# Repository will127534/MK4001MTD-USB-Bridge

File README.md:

# MK4001MTD USB Bridge

**RP2040 Pico firmware that bridges a Toshiba MK4001MTD 0.85" SDIO microdrive as a USB Mass Storage device.**

The MK4001MTD is a 4 GB Microdrive originally used in the Nokia N91 music phone and some other devices, like MP3 players or USB drives, back when flash storage was still quite expensive.

You might have seen introductions claiming this drive uses the MMC protocol, but that’s actually incorrect. I’ve been investigating this for a while: I tried building an 8-bit MMCplus card reader and tested different SD/MMC readers without success. As a last resort, I bought a Nokia N91 to capture logic traces and confirm what protocol it actually uses.

Here is the photo when I was trying to use it with my 8bit-MMCPlus reader board, and it turns out it is not MMC :(

So I end up getting N91 to collect traces:

Unlike standard ATA/CF Microdrives, it uses an SDIO interface with ATA commands tunneled through CMD52/CMD53. No existing driver supports this protocol, so this firmware implements the full stack from scratch.

This surprised me, because there is an SDIO-to-ATA standard called CE-ATA. But if you look closely at the release timeline, CE-ATA came later than this drive. As a result, this drive relies entirely on SDIO commands, and CE-ATA is not available. CE-ATA has two new cmd CMD60/CMD61 and utilize CMD12/39, but you can see from the traces it is not using any of those.  

The second hardware point to mention is that another piece of misinformation floating around—claiming it’s an 8-bit MMCPlus card—is not only untrue, but the pinout doesn’t follow the MMC standard either. You can find the Nokia N91 service manual with some documentation on the pinout: while the pin numbering follows the MMCPlus standard, the pin mapping does not. This is an important detail if you’re wiring it yourself: it uses the same MMC connector, but the pin mapping is different, more in the Hardware section.

Finally, note that this is co-developed with Claude/OpenClaw. I collected the logic traces manually and set up a closed-loop test station for OpenClaw to iterate on development—analyzing the traces and implementing features. The documentation will mostly be written by Claude; I’ll add my notes inline as well. I’ve also read and double-checked the documentation myself, and it should be reliable and easy to follow.

For insights into the analytics on N91 trace, it is under /docs/N91_TRACE_ANALYSIS.md, I've also put the N91 service manual there along with the raw logic traces.

See more in the blog post here: [https://www.willwhang.dev/Reading-MK4001MTD/](https://www.willwhang.dev/Reading-MK4001MTD/)  
See it in activity here: [https://youtu.be/GC4xil3_Bbc](https://youtu.be/GC4xil3_Bbc)

## Status

Fully functional USB mass storage with PIO-accelerated reads/writes and idle power management.

| Metric | Value |
|--------|-------|
| Read speed | ~985 kB/s (USB full-speed limited) |
| Write speed | ~920 kB/s (USB full-speed limited, advertised write cache) |
| Raw SDIO-side speed | ~2.35 MB/s read / ~2.15 MB/s write (drive-limited) |
| Capacity | 3.75 GB (7,862,400 sectors) |
| Filesystem | FAT32 verified (mount/unmount/fsck clean) |
| Data integrity | Write+readback verified; per-block CRC16 on all 4 DAT lines |
| Idle standby | 5 s idle or USB suspend → STANDBY IMMEDIATE + power gate |

## How It Works

### Architecture

```
USB Host ←→ USB MSC (TinyUSB) ←→ ATA Layer ←→ SDIO Layer (PIO) ←→ MK4001MTD
```

The firmware has four layers:

1. **USB MSC** (`msc_device.c`) — TinyUSB Mass Storage Class. Translates SCSI READ(10)/WRITE(10) into ATA sector operations. 32 KB EP buffer, batching up to 64 sectors per USB transfer. Drive I/O is overlapped with USB in both directions, like a real ATA-USB bridge with a caching disk: a sequential-read prefetcher fetches the next chunk while the previous one streams to the host, and writes are staged and flushed while USB receives the next piece. The device advertises its write cache (Caching mode page, WCE=1 — hosts report "Write cache: enabled" and issue SYNCHRONIZE CACHE at fsync/unmount/suspend, which the firmware honors). A failed background flush surfaces as MEDIUM ERROR on the next WRITE or SYNCHRONIZE CACHE; writes to known-bad sectors take a strict synchronous path.

2. **ATA-over-SDIO** (`ata_sdio.c`) — Implements ATA commands (IDENTIFY, READ SECTORS, WRITE SECTORS) by writing to ATA registers mapped into SDIO function 1 address space via CMD52, and transferring sector data via CMD53. 3-tier retry logic at CMD, data, and ATA levels.

3. **PIO SDIO** (`sdio_pio.c`, `sdio.pio`) — Hardware-accelerated SDIO using RP2040's PIO peripheral (4-bit bus at 10 MHz, 4 PIO cycles per bit with input synchronizers bypassed). Three PIO programs share a single state machine via dynamic program swapping:
   - **CMD tx/rx** (24 instructions) — sends SDIO commands and receives responses
   - **DAT read** (12 instructions) — reads data blocks from 4-bit DAT bus via byte-swapping DMA (no CPU repack); block N's CRC verifies while block N+1 streams
   - **DAT write** (14 instructions) — writes data blocks to 4-bit DAT bus via DMA, with built-in CRC status reception and busy-wait; block N+1's nibble stream builds while block N transfers

4. **Pin/Power** (`sdio_hw.c`) — GPIO initialization and HDD power control. All SDIO communication uses PIO.

Human notes: Interestingly, Claude was really reluctant to implement SDIO in PIO, and a lot of development cycles were wasted bouncing back and forth between PIO and bit-banging.

### The SDIO-ATA Protocol

The MK4001MTD presents itself as an SDIO card with one I/O function. Standard SDIO card initialization (CMD5/CMD3/CMD7) sets up the bus, then ATA registers are accessed through SDIO commands:

**Register access (CMD52):** Each ATA register is mapped to a function 1 address:

| Address | Register | Usage |
|---------|----------|-------|
| 0x00 | DATA | CMD53 target for sector data |
| 0x01 | ERR/FEAT | Error (read) / Feature (write) |
| 0x02 | SECCOUNT | Sector count |
| 0x03 | LBA_LO | LBA bits 0-7 |
| 0x04 | LBA_MID | LBA bits 8-15 |
| 0x05 | LBA_HI | LBA bits 16-23 |
| 0x06 | DEV/HEAD | Device/Head + LBA bits 24-27 |
| 0x07 | CMD/STATUS | Command (write) / Status (read) |

**Data transfer (CMD53):** Sector data is transferred by issuing CMD53 in block mode targeting the DATA register (address 0x00). For multi-sector reads, a single CMD53 with `block_count=N` transfers N × 512 bytes in one SDIO multi-block transaction.

**Interrupt signaling:** The drive signals sector readiness by asserting an SDIO interrupt (INT_PENDING bit 1 in CCCR register 0x05). Reading the ATA STATUS register clears the interrupt.

### Read Path (Multi-Block PIO)

For a 16-sector read:

```
1. Write ATA registers via PIO CMD52:
     SECCOUNT=16, LBA_LO/MID/HI, DEV/HEAD=0xE0, CMD=0x20

2. Poll STATUS via CMD52 until DRQ (bit 3) is set

3. Swap PIO to DAT read program
4. Send CMD53: block_mode=1, fn=1, addr=0x0000, block_count=16

5. PIO DAT read: for each of the 16 blocks:
   a. Wait for start bit (all DAT lines low)
   b. DMA 1024 nibbles (512 bytes) from PIO RX FIFO to buffer
   c. Wait for SM to finish clocking CRC+end nibbles (poll SM PC)
   d. Repack nibbles → bytes in-place

6. Swap PIO back to CMD program
```

### Write Path (Multi-Block PIO)

For a 16-sector write:

```
1. Write ATA registers via PIO CMD52:
     SECCOUNT=16, LBA, DEV/HEAD=0xE0, CMD=0x30

2. Poll STATUS via CMD52 until DRQ (bit 3) is set
   (STATUS 0xD8 = BSY+DRQ treated as DRQ-ready, per N91 trace)

3. Swap PIO to DAT write program
4. Send CMD53: block_mode=1, fn=1, addr=0x0000, block_count=16

5. PIO DAT write: for each of the 16 blocks:
   a. Precompute CRC16-CCITT per DAT line (4 independent CRCs)
   b. Build nibble stream: start(0x0) + data(1024 nibbles) + CRC(16) + end(0xF)
   c. DMA nibble stream to PIO TX FIFO
   d. PIO clocks out all nibbles, then:
      - Switches DAT to input
      - Clocks 16 cycles for CRC status from card
      - Polls DAT0 until card releases busy
      - Fires IRQ 0 to signal block completion

6. Swap PIO back to CMD program
```

### PIO Program Swapping

The RP2040 PIO has 32 instruction slots per block. Our three programs total 55 instructions, so they can't coexist. Instead, a single SM0 on PIO0 is used, and programs are swapped by writing directly to PIO instruction memory:

```c
static void load_program_raw(const pio_program_t *program) {
    for (uint i = 0; i < program->length; i++)
        pio->instr_mem[FIXED_OFFSET + i] = program->instructions[i];
}
```

This bypasses the SDK's `pio_add_program`/`pio_remove_program` allocator. Program swap takes ~1 µs. Each swap is followed by a program-specific reinit that sets pin mappings, shift direction, and clock divider.

### Power Management

Analysis of Nokia N91 logic traces reveals aggressive power management:

- **Idle mode:** STANDBY IMMEDIATE (0xE0) every **~7.5 seconds**, even with no I/O. Each standby triggers full SDIO re-initialization (CMD5 retry → CMD3 → CMD7 → CCCR setup). 28 standby cycles observed in one idle session.
- **Active mode:** Standby issued between bursts of I/O (24 cycles during USB drive file operations).
- No other power commands (IDLE, SLEEP, CHECK POWER MODE) or CCCR power register accesses observed.

The firmware replicates this behavior with a configurable idle timeout:

```c
#define IDLE_STANDBY_MS 5000  // in main.c
```

Two paths trigger HDD power gating:

1. **Idle timeout** (5 seconds) — main loop detects no I/O activity
2. **USB suspend** — host suspends the USB port

Both paths send ATA STANDBY IMMEDIATE (0xE0) to flush the write cache and park heads, then cut power via GP9.

**Wake sequence** (triggered by first READ/WRITE after gate):
1. Power on HDD, wait 500ms for rail settling
2. PIO-based SDIO reinit: CMD5 (OCR) → 10ms settle → CMD3 (RCA) → CMD7 (select)
3. Switch to fast PIO clock, configure CCCR via CMD52 (4-bit bus, 512B blocks, fn1 enable)
4. Poll fn1 ready (CCCR IO_READY bit 1)
5. N91-style 30ms DRDY status poll until drive is ATA-ready

### Bad Sector Handling

When a multi-sector transfer hits a bad sector:
1. Chunk read fails → error recovery (IO_ABORT + fn1 reset, ~500ms)
2. Falls back to per-sector I/O to identify the failing block precisely
3. The ATA layer waits long enough to capture the final `STATUS/ERROR` bits instead of collapsing the failure into a generic `DRQ timeout`
4. Any unrecovered block fails the SCSI command immediately with `MEDIUM ERROR` (read: 03/11/00, write: 03/0C/00)
5. Bad-sector LBA cached → repeat *reads* fail quickly without re-hammering the drive (anti-hammer protection against host retry storms)
6. *Writes* always touch the medium, per SBC — a successful write to a cached-bad LBA clears it from the cache, exactly like a drive clearing a pending sector

Point 6 is not academic: this drive had a long-standing unreadable sector at `LBA 1952` (`READ: ST=0x51 ERR ERR=0x40 UNC`). Once the bridge allowed a write to actually reach it, the drive rewrote the sector and it has read back cleanly since:

```text
[ATA] FAST-RD: ST=0x51 ERR ERR=0x40 UNC LBA=1952
[MSC] BAD SECTOR read LBA=1952
[MSC] Bad sector LBA=1952 repaired by write
```

## Building

### Prerequisites

- Raspberry Pi Pico SDK — **stock, unmodified, pinned to 2.2.0**
- ARM toolchain (`arm-none-eabi-gcc`)
- CMake

The SDK version is **locked**: if `PICO_SDK_PATH` is set (environment or
CMake variable) it is used and its version is checked against the pin —
a mismatch fails the configure with instructions (override with
`-DMK4001_ALLOW_SDK_MISMATCH=ON`). With no `PICO_SDK_PATH` at all, the
pinned SDK release is fetched from GitHub automatically at configure
time, so a bare `git clone && cmake && make` is fully reproducible.

The firmware needs a patched TinyUSB MSC class driver (app sense data
preserved on read/write errors + a Caching mode page with WCE=1). That
file is **vendored in this repo** at `lib/tinyusb_patched/msc_device.c` —
the build automatically compiles it instead of the SDK's copy, so no SDK
surgery is ever needed. The diff against upstream TinyUSB (0.18.0, as
bundled with pico-sdk 2.2.0) is in `lib/tinyusb_patched/`; the SDK pin
exists precisely because this vendored file must track the SDK's TinyUSB.

### Build & Flash

```bash
cd /home/pi/mk4001_bridge/build
cmake ..
make -j4

sudo openocd -f interface/cmsis-dap.cfg -f target/rp2040.cfg \
  -c "adapter speed 1000" -c "init" -c "reset halt" -c "sleep 200" \
  -c "program /home/pi/mk4001_bridge/build/mk4001_bridge.elf verify" \
  -c "reset run" -c "exit"
```

### Hardware Wiring

| Pico GPIO | Function | Notes |
|-----------|----------|-------|
| GP2 | SDIO_CLK | Host clock output |
| GP3 | SDIO_CMD | Bidirectional command line |
| GP4 | SDIO_DAT0 | Data bit 0 |
| GP5 | SDIO_DAT1 | Data bit 1 |
| GP6 | SDIO_DAT2 | Data bit 2 |
| GP7 | SDIO_DAT3 | Data bit 3 |
| GP9 | HDD_EN | Drive power enable (HIGH=on) |
| GP12 | UART TX | Debug output @ 115200 |
| GP13 | UART RX | Debug input |
| GP16 | LED: HDD Power | Active low |
| GP17 | LED: HDD Healthy | Active low |
| GP18 | LED: Read | Active low |
| GP19 | LED: Write | Active low |

**Note:** GP0 and GP1 are dead on this specific Pico unit. All SDIO pin assignments are shifted +2.

Human notes: Claude was wrong here because it didn’t realize that GP0 and GP1 were being used for the UART terminal in its build configuration. It kept forgetting this, to the point where I just moved the SDIO GPIOs off that UART.

HDD_PWR isn’t necessary. You don’t have to power-cycle the drive to use it; it’s more of a development convenience for resetting the HDD when a lot of things are hard-coded. That said, if you want power savings, you can use that signal, but it can handle warm reset without any issue.

You’ll see debug messages over UART. They’re not going through USB-CDC because it was easier for Claude to set up a separate UART-to-USB logging link that doesn’t disconnect or become unstable during early development.

The UART log also reports the **drive temperature** every 30 seconds while the drive is active (`[TEMP] drive temperature: 29 C`). The sensor was discovered by reverse-engineering the Toshiba vendor command `0xC2` — the N91 reads it at the start of every drive session to enforce its HDD operating-temperature limits. Details in [`docs/N91_TRACE_ANALYSIS.md`](docs/N91_TRACE_ANALYSIS.md) §4.

Here is a example of the log:

```
========================================
  MK4001MTD USB Bridge v0.11
  SDIO-ATA → USB Mass Storage (PIO)
========================================

[MAIN] Pre-delay 5000ms...
[PIO] Init OK: clkdiv=3.12 (~10.0 MHz), CMD@0
[MAIN] Power cycling HDD...
[SDIO] HDD power OFF
[SDIO] HDD power ON
[MAIN] SDIO init (PIO)...
[SDIO] CMD5 ready (OCR=0x901F8000)
[SDIO] RCA=0x0001
[SDIO] fn1 ready (attempt 0)
[MAIN] ATA IDENTIFY...
[ATA] IDENTIFY complete
Model:    [TOSHIBA MK4001MTD]
Serial:   [           763B004HA]
Firmware: [VH173A]
Sectors:  7862400 (3839 MB)
SMART:    not supported (supported=0, enabled=0)
IDENTIFY: W0=0040 W47=0000 W49=0000 W59=0000
  ATA W80=0000  Cmd W82=0000 W83=0000 W84=0000
  En  W85=0000 W86=0000 W87=0000  W89=0008 W128=0001

[DIAG] === Drive Diagnostics ===
[DIAG] Standard SMART: not supported (IDENTIFY W82 bit0 = 0)
[DIAG] Toshiba vendor CMD 0xC2:
  FEAT=0x01 unknown_01                       → SC=00 LBA=02/00/00 ST=50
  FEAT=0x02 unknown_02                       â SC=00 LBA=02/00/00 ST=50
  FEAT=0x03 unknown_03                       → SC=00 LBA=02/00/00 ST=50
  FEAT=0x04 unknown_04                       → SC=00 LBA=02/00/00 ST=50
  FEAT=0x10 diag_10 (LBA_LO varies)          → SC=00 LBA=00/00/00 ST=50
  FEAT=0x11 diag_11                          → SC=00 LBA=00/00/00 ST=50
  FEAT=0x12 diag_12 (LBA_LO varies)          → SC=00 LBA=01/00/00 ST=50
  FEAT=0x20 query_20 (N91: SC=0xFF always)   → SC=FE LBA=00/FF/00 ST=50
  FEAT=0x21 query_21 (N91: SC varies per boot) → SC=1B LBA=00/FF/00 ST=50

[MAIN] MBR: valid 0x55AA
[MAIN] Warming up...
[MAIN] PIO OK, STATUS=0x50
[MAIN] Drive: 7862400 sectors (3839 MB)
[MAIN] Ready.
[PWR] Idle 5000ms → STANDBY + power gate
[PWR] STANDBY IMMEDIATE → power gate
[SDIO] HDD power OFF
```

Finally, here’s the wiring to the actual drive.  

Here is a crop from the N91 schematic, you can map the pin number also.

Side note that this is a 3V drive but I think 3.3V is fine, mostly it is to save some level shifting work.  

HW specifically designed for this drive is under /hardware!

## Source Files

| File | Lines | Purpose |
|------|-------|---------|
| `main.c` | 210 | Init, idle standby, USB suspend/resume |
| `msc_device.c` | 400 | USB MSC callbacks, power gate wake, bad sector cache |
| `ata_sdio.c` | 390 | ATA commands, error recovery, vendor diagnostics |
| `sdio_pio.c` | 635 | PIO SDIO: CMD52, CMD53 read/write, program swap, CRC16 |
| `sdio_hw.c` | 45 | Pin init + HDD power control |
| `sdio.pio` | 200 | PIO assembly + C SDK init helpers |
| `led.h` | 37 | LED helpers (GP16–GP19, active low) |
| `usb_descriptors.c` | 77 | USB device/config/string descriptors |
| `tusb_config.h` | 20 | TinyUSB config (MSC, 32KB EP buffer) |

## Version History

| Version | Read | Write | Key Change |
|---------|------|-------|------------|
| v0.1–v0.3 | 105 kB/s | 93 kB/s | Bit-bang SDIO, CRC16, retry logic |
| v0.5 | 374 kB/s | — | Single-SM PIO, direct instruction memory swap |
| v0.6 | 583 kB/s | 93 kB/s | Multi-block CMD53 reads, CRC clock drain fix |
| v0.8 | 588 kB/s | 274 kB/s | PIO writes, OSR flush fix |
| v0.9 | 475 kB/s | 371 kB/s | 64-sector chunks, CRC16 read verification |
| v0.10 | 453 kB/s | 329 kB/s | LED remap, HDD EN pin, UART on GP12/GP13 |
| v0.11 | ~450 kB/s | ~340 kB/s | HDD power gate, PIO wake, bad sector sense, USB suspend |
| **v0.12** | **~985 kB/s** | **~920 kB/s** | **Drive/USB overlap (read prefetch + advertised write cache with write-behind), pipelined PIO blocks, bswap DMA, 4-cycle PIO loops, SBC-style bad-sector semantics (write-repair), vendored TinyUSB MSC driver** |

## Testing

```bash
# Check device appeared
lsblk -dno NAME,MODEL | grep MK4001

# Filesystem test — mount, copy files, verify
sudo mount /dev/sdX1 /mnt/mk4001
cp /tmp/testfile /mnt/mk4001/
sync
md5sum /tmp/testfile /mnt/mk4001/testfile    # should match
sudo umount /mnt/mk4001

# Speed benchmarks (raw device, do NOT mount first — will corrupt filesystem)
# Use a safe offset past the filesystem or an unpartitioned drive
sudo dd if=/dev/sdX of=/dev/null bs=64k count=128 iflag=direct     # read
sudo dd if=/dev/zero of=/dev/sdX bs=64k count=64 oflag=direct seek=1024  # write (offset past FS)
```

Human notes here, fun fact: When it first starts to do speed testing, it actually dd directly to the drive and damage the filesystems..... Thankfully it doesn't matter that much here during the developments but always keep in mind when you handle OpenClaw your setup.

## License

I don't care.

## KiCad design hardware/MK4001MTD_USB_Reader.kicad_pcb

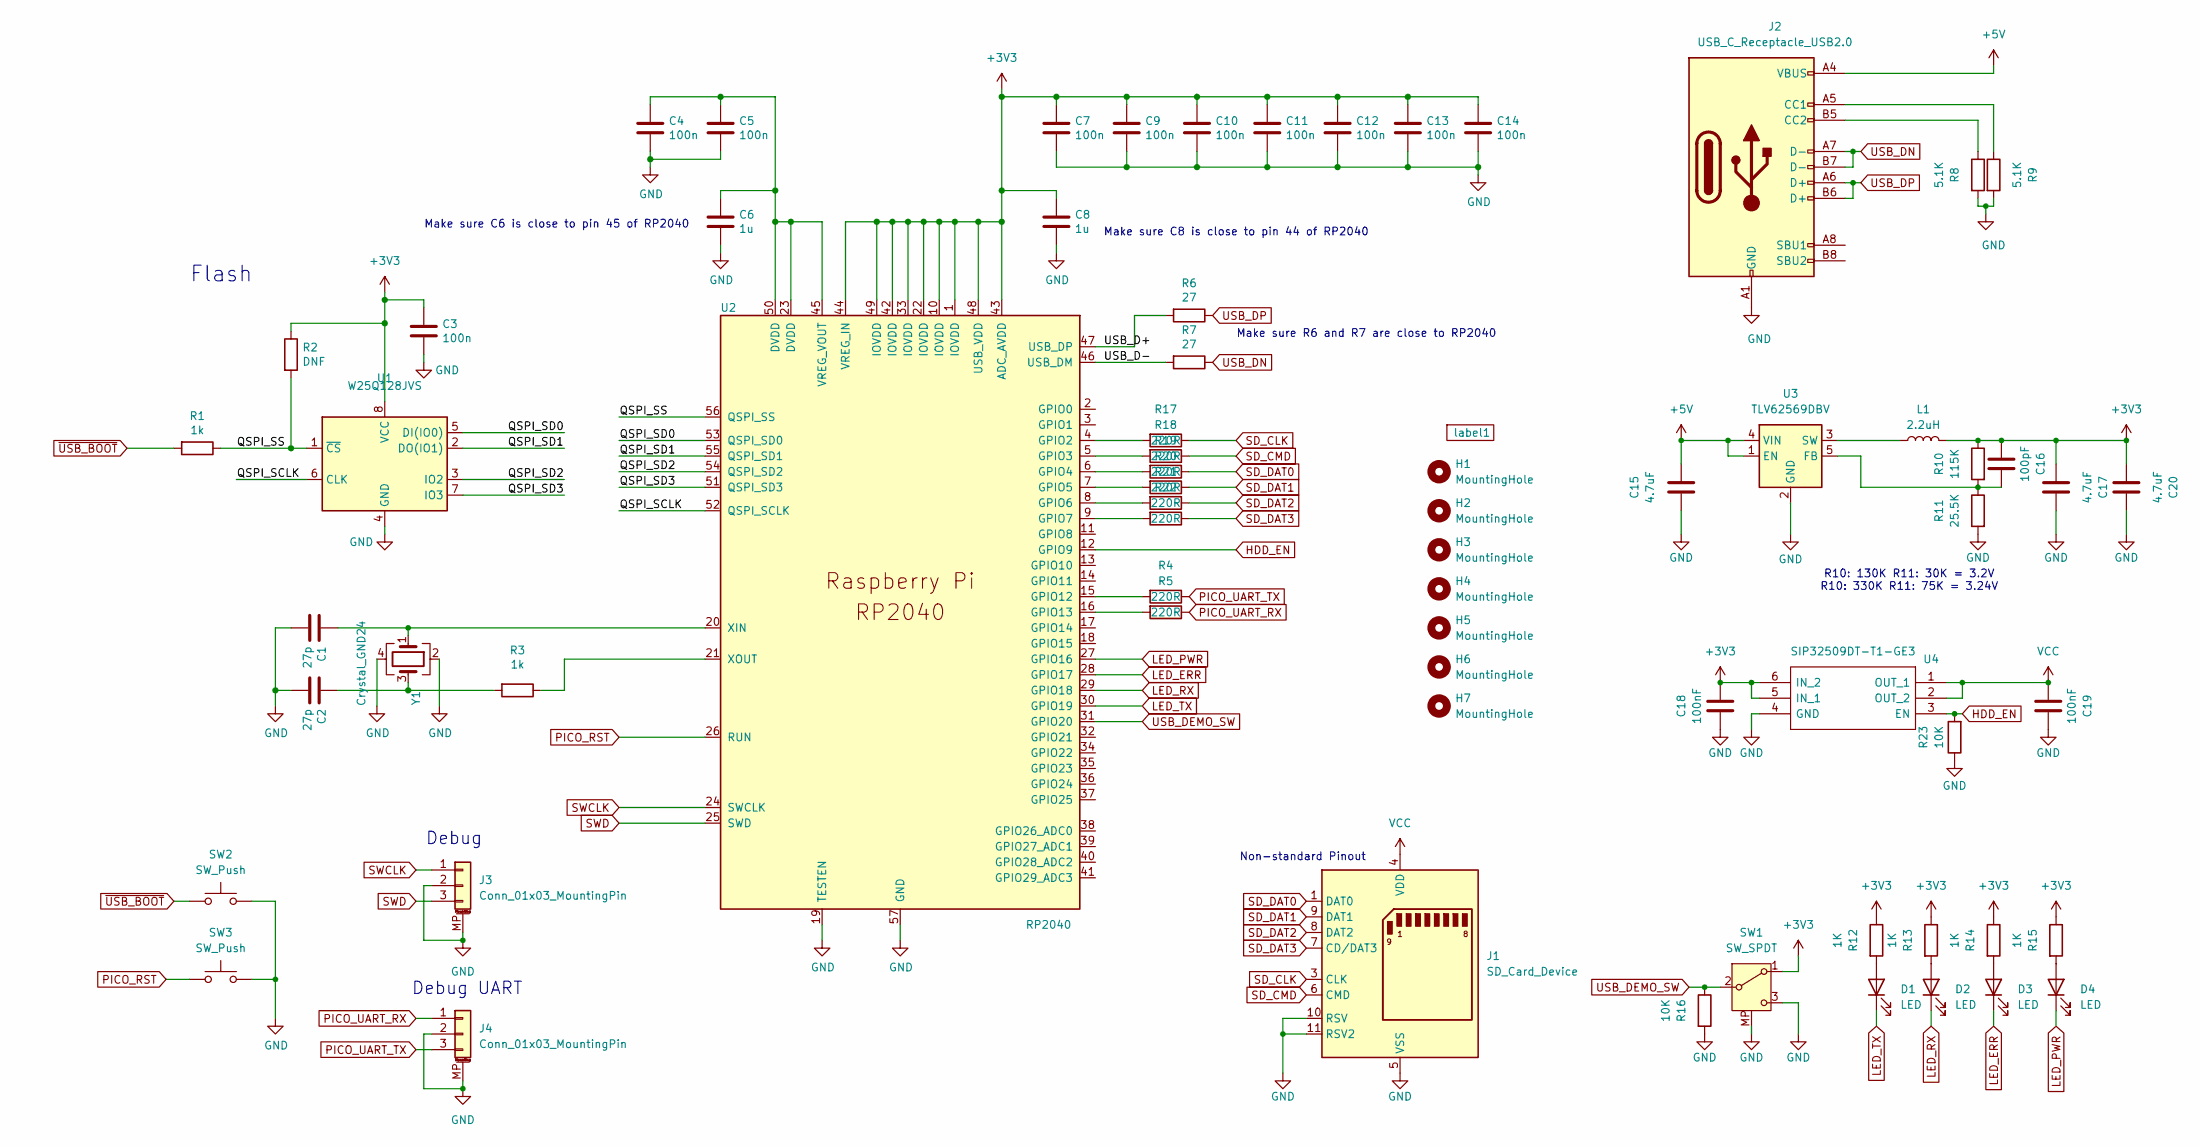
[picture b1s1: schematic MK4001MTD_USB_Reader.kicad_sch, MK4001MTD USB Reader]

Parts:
C1, C2: 27p; C_0402_1005Metric
C3, C4, C5, C7, C9, C10, C11, C12, C13, C14: 100n; C_0402_1005Metric
C6, C8: 1u; C_0402_1005Metric
C15: 4.7uF; C_0603_1608Metric
C16: 100pF; C_0402_1005Metric
C17, C20: 4.7uF; C_0805_2012Metric
C18: 100nF; C_0402_1005Metric
C19: 100nF; C_0805_2012Metric
D1, D2, D3, D4: LED; LED_0603_1608Metric
H1, H2, H3, H4, H5, H6, H7: MountingHole; MountingHole_2.2mm_M2
J1: SD_Card_Device; MK4001MTD
J2: USB_C_Receptacle_USB2.0; USB_C_Receptacle_XKB_U262-16XN-4BVC11
J3, J4: Conn_01x03_MountingPin; JST_SH_SM03B-SRSS-TB_1x03-1MP_P1.00mm_Horizontal
L1: 2.2uH; L_Vishay_IHLP-2020
R1, R3: 1k; R_0402_1005Metric
R2: DNF; R_0402_1005Metric
R4, R5, R17, R18, R19, R20, R21, R22: 220R; R_0402_1005Metric
R6, R7: 27; R_0402_1005Metric
R8, R9: 5.1K; R_0402_1005Metric
R10: 115K; R_0402_1005Metric
R11: 25.5K; R_0402_1005Metric
R12, R13, R14, R15: 1K; R_0402_1005Metric
R16, R23: 10K; R_0402_1005Metric
SW1: SW_SPDT; SW_SPDT_PCM12
SW2, SW3: SW_Push; SW_Tactile_SPST_NO_Straight_CK_PTS636Sx25SMTRLFS
U1: W25Q128JVS; DFN-8-1EP_3x2mm_P0.5mm_EP1.36x1.46mm
U2: RP2040; RP2040-QFN-56
U3: TLV62569DBV; SOT-23-5
U4: SIP32509DT-T1-GE3; SOT-23-6; Mouser Part Number 78-SIP32509DT-T1-GE3
Y1: Crystal_GND24; Crystal_SMD_3225-4Pin_3.2x2.5mm
label1: QRCode

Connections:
+3V3: C3.1, C7.1, C8.1, C9.1, C10.1, C11.1, C12.1, C13.1, C14.1, C16.1, C17.1, C18.2, C20.1, L1.2, R2.1, R10.1, R12.1, R13.1, R14.1, R15.1, SW1.1 (A), U1.8 (VCC), U2.1 (IOVDD), U2.10 (IOVDD), U2.22 (IOVDD), U2.33 (IOVDD), U2.42 (IOVDD), U2.43 (ADC_AVDD), U2.44 (VREG_IN), U2.48 (USB_VDD), U2.49 (IOVDD), U4.5 (IN_1), U4.6 (IN_2)
+5V: C15.2, J2.A4 (VBUS), J2.A9 (VBUS), J2.B4 (VBUS), J2.B9 (VBUS), U3.1 (EN), U3.4 (VIN)
/QSPI_SCLK: U1.6 (CLK), U2.52 (QSPI_SCLK)
/QSPI_SD0: U1.5 (DI(IO0)), U2.53 (QSPI_SD0)
/QSPI_SD1: U1.2 (DO(IO1)), U2.55 (QSPI_SD1)
/QSPI_SD2: U1.3 (IO2), U2.54 (QSPI_SD2)
/QSPI_SD3: U1.7 (IO3), U2.51 (QSPI_SD3)
/QSPI_SS: R1.1, R2.2, U1.1 (~CS), U2.56 (QSPI_SS)
/USB_D+: R6.2, U2.47 (USB_DP)
/USB_D-: R7.2, U2.46 (USB_DM)
GND: C1.2, C2.2, C3.2, C4.2, C5.2, C6.2, C7.2, C8.2, C9.2, C10.2, C11.2, C12.2, C13.2, C14.2, C15.1, C17.2, C18.1, C19.2, C20.2, J1.2 (VSS), J1.5 (VSS), J1.10 (RSV), J1.11 (RSV2), J2.A1 (GND), J2.A12 (GND), J2.B1 (GND), J2.B12 (GND), J3.2, J3.MP (MountPin), J4.2, J4.MP (MountPin), R8.2, R9.2, R11.2, R16.2, R23.1, SW1.3 (C), SW1.MP, SW2.2, SW3.2, U1.4 (GND), U2.19 (TESTEN), U2.57 (GND), U3.2 (GND), U4.4 (GND), Y1.2, Y1.4
HDD_EN: R23.2, U2.12 (GPIO9), U4.3 (EN)
LED_ERR: D3.1 (K), U2.28 (GPIO17)
LED_PWR: D4.1 (K), U2.27 (GPIO16)
LED_RX: D2.1 (K), U2.29 (GPIO18)
LED_TX: D1.1 (K), U2.30 (GPIO19)
unnamed: C2.1, R3.2, Y1.3
unnamed: D1.2 (A), R12.2
unnamed: D2.2 (A), R13.2
unnamed: D3.2 (A), R14.2
unnamed: D4.2 (A), R15.2
unnamed: J2.A5 (CC1), R9.1
unnamed: J2.B5 (CC2), R8.1
unnamed: R17.2, U2.4 (GPIO2)
unnamed: R18.2, U2.5 (GPIO3)
unnamed: R19.2, U2.6 (GPIO4)
unnamed: R20.2, U2.7 (GPIO5)
unnamed: R21.2, U2.8 (GPIO6)
unnamed: R22.2, U2.9 (GPIO7)
unnamed: R4.2, U2.15 (GPIO12)
unnamed: R5.2, U2.16 (GPIO13)
unnamed: C4.1, C5.1, C6.1, U2.23 (DVDD), U2.45 (VREG_VOUT), U2.50 (DVDD)
unnamed: C1.1, U2.20 (XIN), Y1.1
unnamed: R3.1, U2.21 (XOUT)
unnamed: C16.2, R10.2, R11.1, U3.5 (FB)
unnamed: L1.1, U3.3 (SW)
PICO_RST: SW3.1, U2.26 (RUN)
PICO_UART_RX: J4.1, R5.1
PICO_UART_TX: J4.3, R4.1
SD_CLK: J1.3 (CLK), R17.1
SD_CMD: J1.6 (CMD), R18.1
SD_DAT0: J1.1 (DAT0), R19.1
SD_DAT1: J1.9 (DAT1), R20.1
SD_DAT2: J1.8 (DAT2), R21.1
SD_DAT3: J1.7 (CD/DAT3), R22.1
SWCLK: J3.1, U2.24 (SWCLK)
SWD: J3.3, U2.25 (SWD)
USB_DEMO_SW: R16.1, SW1.2 (B), U2.31 (GPIO20)
USB_DN: J2.A7 (D-), J2.B7 (D-), R7.1
USB_DP: J2.A6 (D+), J2.B6 (D+), R6.1
VCC: C19.1, J1.4 (VDD), U4.1 (OUT_1), U4.2 (OUT_2)
~USB_BOOT: R1.2, SW2.1

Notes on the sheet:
Debug UART
Make sure R6 and R7 are close to RP2040
Flash
Make sure C8 is close to pin 44 of RP2040
Debug
R10: 130K R11: 30K = 3.2V R10: 330K R11: 75K = 3.24V
Make sure C6 is close to pin 45 of RP2040
Non-standard Pinout

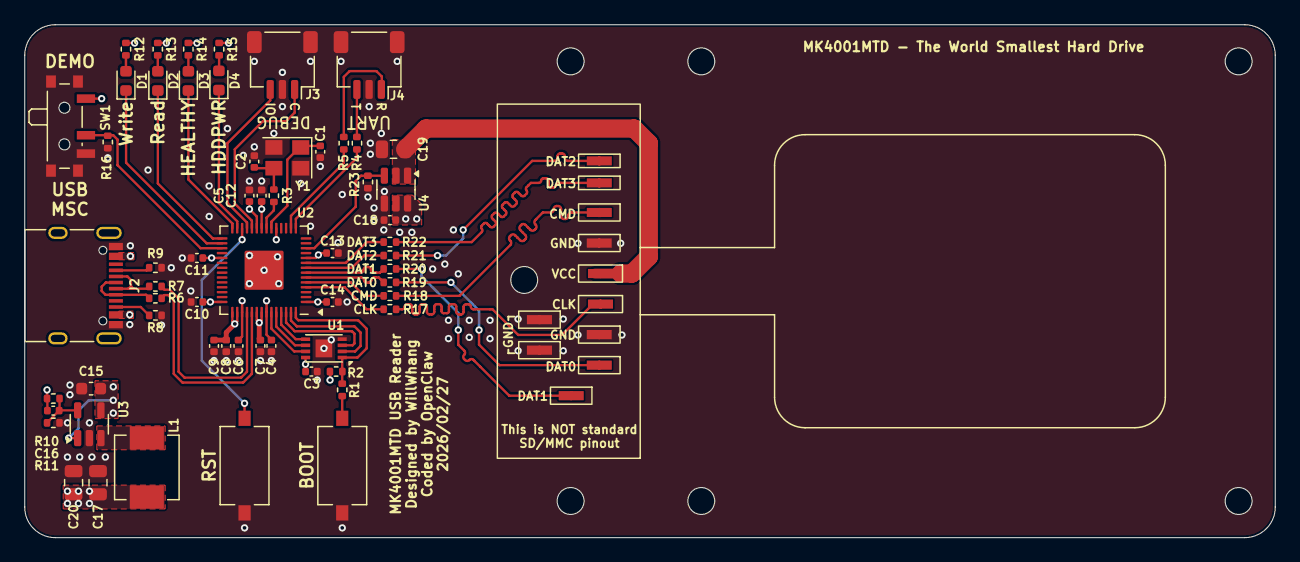
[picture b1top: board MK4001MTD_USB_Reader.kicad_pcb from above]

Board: 4 copper layers, 102.4 x 42.0 mm, 68 parts (1 on the bottom side), 52 nets.

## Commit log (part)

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2026-03-01 init
2026-03-01 Enhance README with images and hardware information
    Added images and clarified hardware details in the README.
2026-03-01 Update README with protocol and pinout clarifications
    Clarified the differences between the drive's protocol and CE-ATA standards, and corrected misinformation about the MMCPlus card pinout.
2026-03-16 Adding V0.11 code and HW design
2026-03-16 Add blog post link for additional information
    Added a link to the blog post for further insights.
2026-03-16 Add YouTube link for project activity
    Added a link to a YouTube activity related to the project.
2026-03-19 Adding support for warm boot - specifically tested on breadboard
